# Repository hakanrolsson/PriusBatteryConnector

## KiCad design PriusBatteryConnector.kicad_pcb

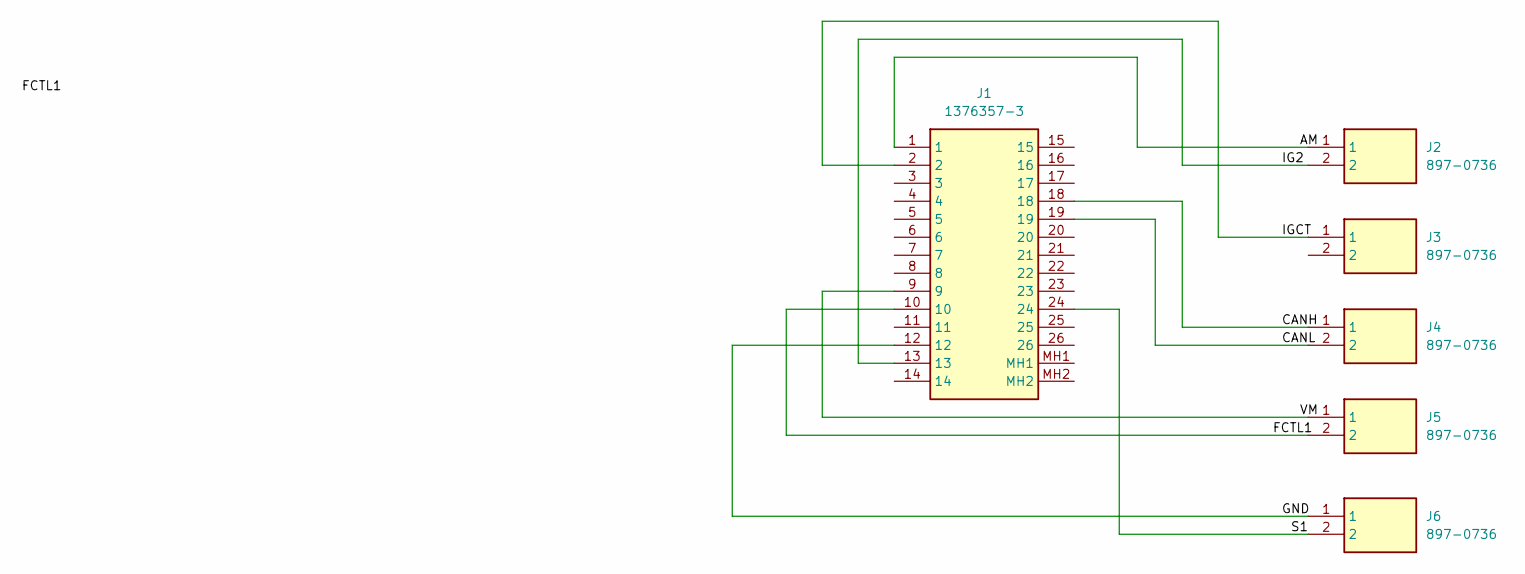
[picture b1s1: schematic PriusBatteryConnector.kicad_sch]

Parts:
J1: 1376357-3; 13763573; Manufacturer_Part_Number 1376357-3; Mouser Part Number 571-1376357-3
J2, J3, J4, J5, J6: 897-0736; SHDR2W100P0X500_1X2_1060X760X1020P; Manufacturer_Part_Number 897-0736

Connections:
/AM: J1.1, J2.1
/CANH: J1.18, J4.1
/CANL: J1.19, J4.2
/FCTL1: J1.10, J5.2
/GND: J1.12, J6.1
/IG2: J1.13, J2.2
/IGCT: J1.2, J3.1
/S1: J1.24, J6.2
/VM: J1.9, J5.1

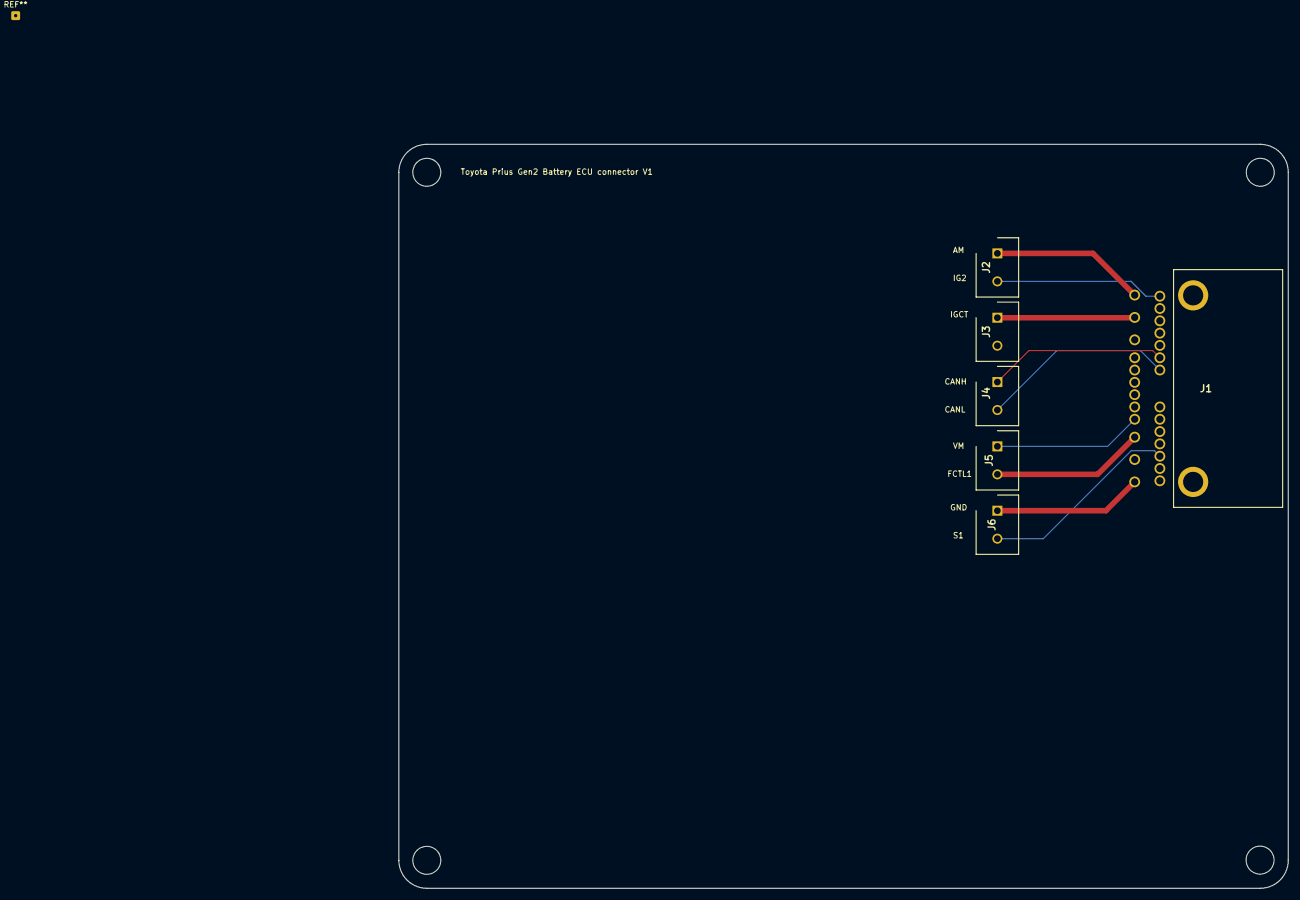
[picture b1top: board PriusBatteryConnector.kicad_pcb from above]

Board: 2 copper layers, 159.0 x 133.0 mm, 6 parts (0 on the bottom side), 9 nets.

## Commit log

2025-01-01 Add files via upload
    V1 of PriusBatteryConnector
